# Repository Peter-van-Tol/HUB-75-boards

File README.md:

# HUB-75 boards

The HUB-75 boards is a collection of break-out boards (BOBs) for HUB-75 connnectors found on re-purposed FPGA cards such as the 5A-75B and 5A-75E. These cards can be picked up for 10\~20 dollars from China and form an ideal basis for tinkering with FPGAs. Based on these cheap FPGA's a project has been spraked, called Litex-CNC, which aims to repurpose these cards to a cheap CNC controller. CNC-machines normally have field power which is 12\~24V and thus the FPGA cannot direclty be connected to the components of the machine. Therefore a set of break-out boards have been developed for GPIO inputs/outputs, stepgen, encoders, etc.

## Design philosophy
> Why not a hat one might ask? This project offers more flexibility. By combining different break-out can be combined to suit the machine that is being built. A hat also comes with a larger risk in design errors; smaller boards are easier to design, produce and check.

All BOBs will have the same dimensions of 85 mm x 56 mm. This size is equal to that of the Raspberry Pi 4, however the mounting holes are placed on the four corners and thus different from the RPi. Getting the mounting holes at the same location as the RPi made the design much more difficult. Placement of the connectors also hampers stacking these boards on top of each other, so not being to able to stack them on top of a RPi seems permissible.

The outputs of the BOBs will be on the bottom edge (long side). Field power and logic power are provided from the left side of the board. The HUB-75 connectors will be placed on the top of the boards. This makes it easier to route the digital signals and high-power signals separately from each other in the cabinet.

The smalles trace and spacing is 0.2 mm. These boards are designed to be ordered from an online PCB manufacturer. Some desktop milling machines might have the accuracy to create these traces, so you might give it a try when you are feeling lucky. The smallest holes (vias) are 0.3 mm in size.

All components are selected to be hand-solderable. This means that the following minimum sizes SMD components will be used:
- resistors, LED's, capacitors: SMD-1206
- diodes: SOD-123
- FET, transistors: SOT-23

## HUB-75 pinout
Each connector has 6 individual pins (1, 2, 3, 5, 6, and 7) and 8 shared pins (8 through 15). The standard pin-out of a HUB-75 connector is shown below.

| HUB75 pin | Pin   | Pin   | HUB75 pin |
|-----------|-------|-------|-----------|
| R0        | 1     | 2     | G0        |
| B0        | 3     | 4     | *GND*     |
| R1        | 5     | 6     | G1        |
| B1        | 7     | 8     | E         |
| A         | 9     | 10    | B         |
| C         | 11    | 12    | D         |
| CLK       | 13    | 14    | STB       |
| OE        | 15    | 16    | *GND*     |

Each HUB-75 connector will use the individual pins and in special cases one of the shared pins. In the design it should be taken into account that boards which uses the same shared pins might be mutual exclusive when the functions are different (different types of stepgen BOBs can off course be combined.

## Available BOBs
The table below shows the BOBs which are currently available in this repository, along with their status.

| Category  | Name                                                     | Description                                                     | HUB-75    | Status            |
|-----------|----------------------------------------------------------|-----------------------------------------------------------------|-----------|---------------------|
| stepgen   | [HUB75-Differential_stepgen](HUB75-Differential_stepgen) | 3 differential stepgen channels, frequency up to 400 kHz        | 2 + 0.5   | Prototype-2 ordered | 
| GPIO-out  | [HUB75-Sourcing_output](HUB75-Sourcing_output)           | 12 channel sourcing output (<1 kHz, 4 A per channel, 4 A total) | 2         | Prototype-2 ordered | 
| GPIO-in   | [HUB75-Sinking_input](HUB75-Sinking_input)               | 12 channel sinking input (< 1 kHz)                              | 2         | Untested          |

## Connecting the BOBs to your FPGA
On both the 5A-75B and the 5A-75E the `74HC245T` buffers are hard-wired as outputs. To be able to use the HUB-75 boards which require an input (as seen from the FPGA) some modifications on the board are required. Of both boards different versiosn exist, so the components can be at a different location on your board. Below are the locations of the buffer on a 5A-75B V6.1 (front) and 5A-75E V6.0 (back).

Each buffer has 8 channels, while every HUB-75 connector has 6 individual pins. When you replace a buffer you will cahnge the behavior of one HUB-75 connector and partly that of its neighbor. All HUB-75 boards assume that a connector is either fully configured as input or as output. Therefore it is recommended to change the buffers direclty adjacent to each other, so the minimum amount of available connectors (partly input/ouput) are wasted.

The following changes have to be made to the buffers:
* De-solder the `74HC245T` buffer, this buffer cannot be re-used because its pins are not 5 Volt tolerant when `Vcc` is 3.3 Volt.
* Cut the trace to the pin `Vcc` (pin 20) and wire it to a 3.3V source (for example the JTAG-header). If you don't do this, a buffer configure as input will put 5 Volts on the pins of the FPGA, which will definately fry that pin or the whole board.
* Cut the trace to the pin `DIR` (pin 20) and wire it to a GND source to configure the buffer as input.
* Replace the buffer with a buffer with 5V tolerant inputs, such as the `74LVC245` ([datasheet](https://www.ti.com/lit/ds/symlink/sn74lvc245a.pdf)).

After these modifications the board might look a like this (on this particular board a single buffer has been replace, as it is a test-board for LitexCNC).

TODO: picture to be taken

## License 
The boards in this repository are licensed unde Creative Commons BY-NC-SA. This means you are allowed to:
* **Share** — copy and redistribute the material in any medium or format
* **Adapt** — remix, transform, and build upon the material

As long as:
* **Attribution** — You must give appropriate credit, provide a link to the license, and indicate if changes were made. You may do so in any reasonable manner, but not in any way that suggests the licensor endorses you or your use.
* **NonCommercial** — You may not use the material for  commercial purposes. Of course you can use the machine you created or modified using these boards for commercial purposes. 
* **ShareAlike** — If you remix, transform, or build upon the material, you must distribute your contributions under the  same license  as the original.

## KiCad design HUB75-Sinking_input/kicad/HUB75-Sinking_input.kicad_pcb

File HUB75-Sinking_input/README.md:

# HUB-75 Sinking input 
Break-out board with 12 channel sinking input. The FPGA is galvanically separated from field power using opto-couplers.

## Features

- 2 HUB-75 output connectors
- 12 channel sinking output using JST connectors
- 5\~24 V Field power with reverse polarity protection
- indicating LED for each output
- indicated switching frequency 1 kHz

## Applications

- PNP (souring) limit switches
- Momentary push-buttons
- Slow encoders, for example for user input

> **NOTE** <br> The `PC827` optocouplers have a maximum rated frequency of 80 kHz. It is recommended to start at a frequency of 1 kHz and work up from there.

## Example wiring

TODO: example

## Litex-CNC example configuration
Let's assume that the two HUB-745 connectors on this board are connected to J15 and J16 of the FPGA. To configure the pins for output, you can use the configuration-block below as a starting point. Optionaly the pin names can also be set in the configuration, making the HAL clearer.

``` json
{
    ...,
    "gpio_in": [
        {"pin": "j15:0"},
        {"pin": "j15:1"},
        {"pin": "j15:2"},
        {"pin": "j15:4"},
        {"pin": "j15:5"},
        {"pin": "j15:6"},
        {"pin": "j16:0"},
        {"pin": "j16:1"},
        {"pin": "j16:2"},
        {"pin": "j16:4"},
        {"pin": "j16:5"},
        {"pin": "j16:6"}
    ],
    ...
}
```

Alternatively, the BOB can also be used for PWM output. In that case the configuration may look something like below. In this example it is assumed that outputs on J16 are used for three encoders.

``` json
{
    ...,
    "encoders": [
        {  
            "pin_A":"j16:0",
            "pin_B":"j16:1"
        },
        {  
            "pin_A":"j16:2",
            "pin_B":"j16:4"
        },
        {  
            "pin_A":"j16:5",
            "pin_B":"j16:6"
        }
    ],
    ...
}
```

## Bill of materials

The table below gives the bill of materials used for this BOB and an indication of its price. The list is available as public list for the following companies:
* [Reichtelt](https://www.reichelt.de/my/1998173). This is non-affiliate link, I do not earn any money when you order this list from this specific vendor, nor the vendor endorses this project. Reichtelt is a supplyer for Western Europe.

When you order with Mouser or antohter supplier, please share a list here.

| Part. number | Package   | Description                        | Datasheet | Amount | Price*  |
|--------------|-----------|------------------------------------|-----------|--------|---------|
| LTV827       | DIP-8     | Dual-channel opto-coupler          |           | 6      | € 0.31  |
| AO3401A      | SOT-23    | P-Channel MOSFET, 30V              |           | 1      | € 0.25  |
| ZENER 12V    | SOT-23    | 12V Zener diode***                 |           | 1      | € 0.05  |
| 4.7K         | SMD 1206  | Resistor, 4.7 kOhm                 |           | 12     | € 0.03  |
| 10K          | SMD 1206  | Resistor, 10 kOhm                  |           | 1      | € 0.03  |
| LED          | SMD 1206  | LED, green, If > 20 mA             |           | 12     | € 0.08  |
| CAP 15N      | SMD 1206  | Capitor, 15 nF                     |           | 1      | € 0.02  |
| JST XH 3P    | -         | JST XH conn. 2.5 mm pitch          |           | 12     | € 0.15  |
| DG250 3,5-2  | -         | Screw/spring terminal 2.5 mm pitch |           | 2      | € 0.22  |
| BOX 2X8      | -         | Box header 2x8, 2.54 mm pitch      |           | 2      | € 0.16  |
| 2N7002**     | SOT-23    | N-Channel MOSFET (current mirror)  |           | 13     | € 0.04  |
| CL2N8-G**    | SOT-89    | LED-driver 20 mA (current mirror)  |           | 1      | € 0.39  |
| R**          | SMD 1206  | Resistor, TBD Ohm (alternative)    |           | 12     | € 0.03  |

**NOTES**: 
1. The price is based on availability in the Netherlands with a single shop for all parts. Parts might be sourced cheaper depending on your location, available sources and the time you want to wait before receiving the components.
2. The components `CL2N8-G` and `2N7002` form a current mirror for driving the status LEDs. This current mirror can be replaced with a fixed resistor `R`, which should be calculated based on the voltage used for Field power.
3. The zener diode is only required when Field Power is >12 Volt for protecting the MOSFETs.

## Known issues

This board does not have any known issues yet.

If you find any issue, please file a bug using GitHub.

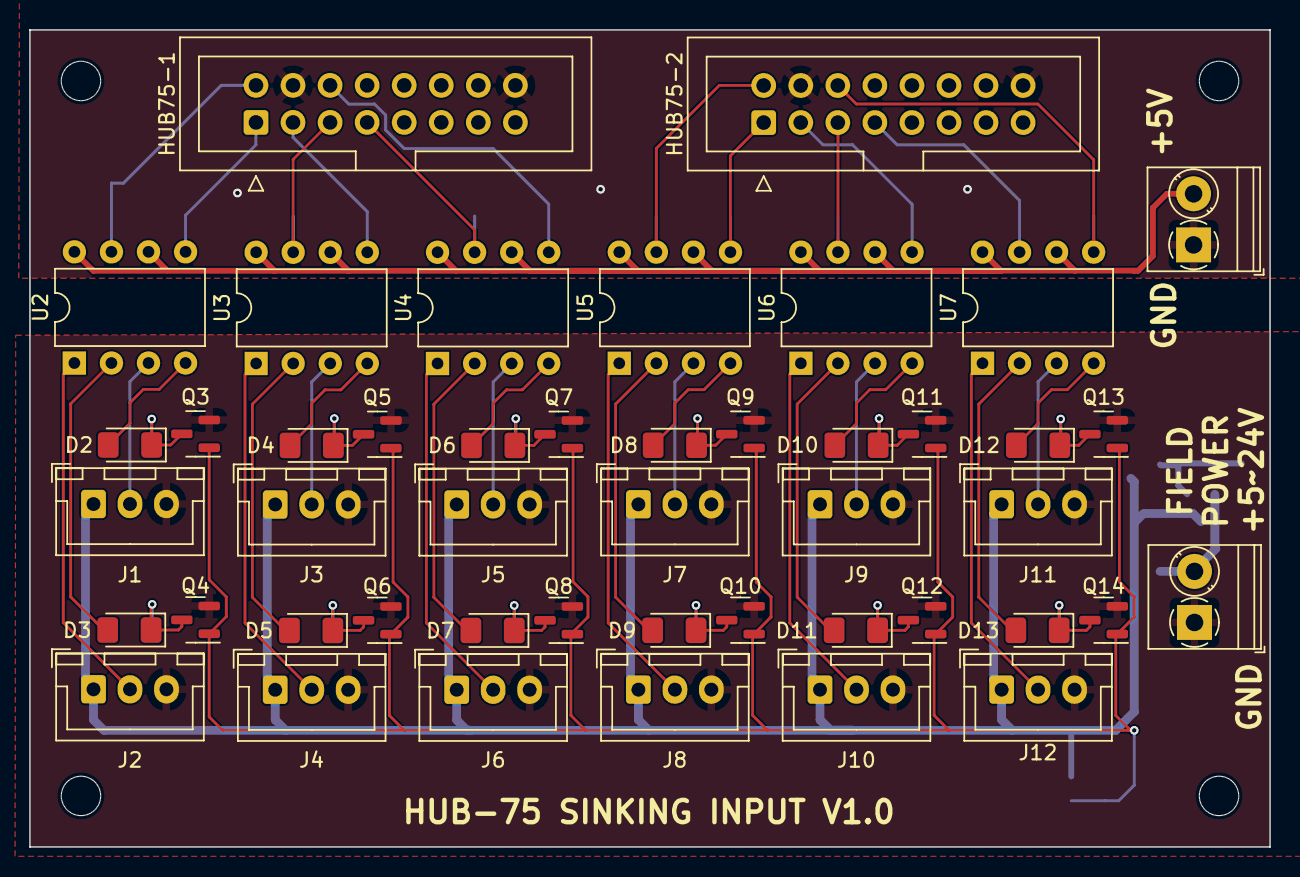
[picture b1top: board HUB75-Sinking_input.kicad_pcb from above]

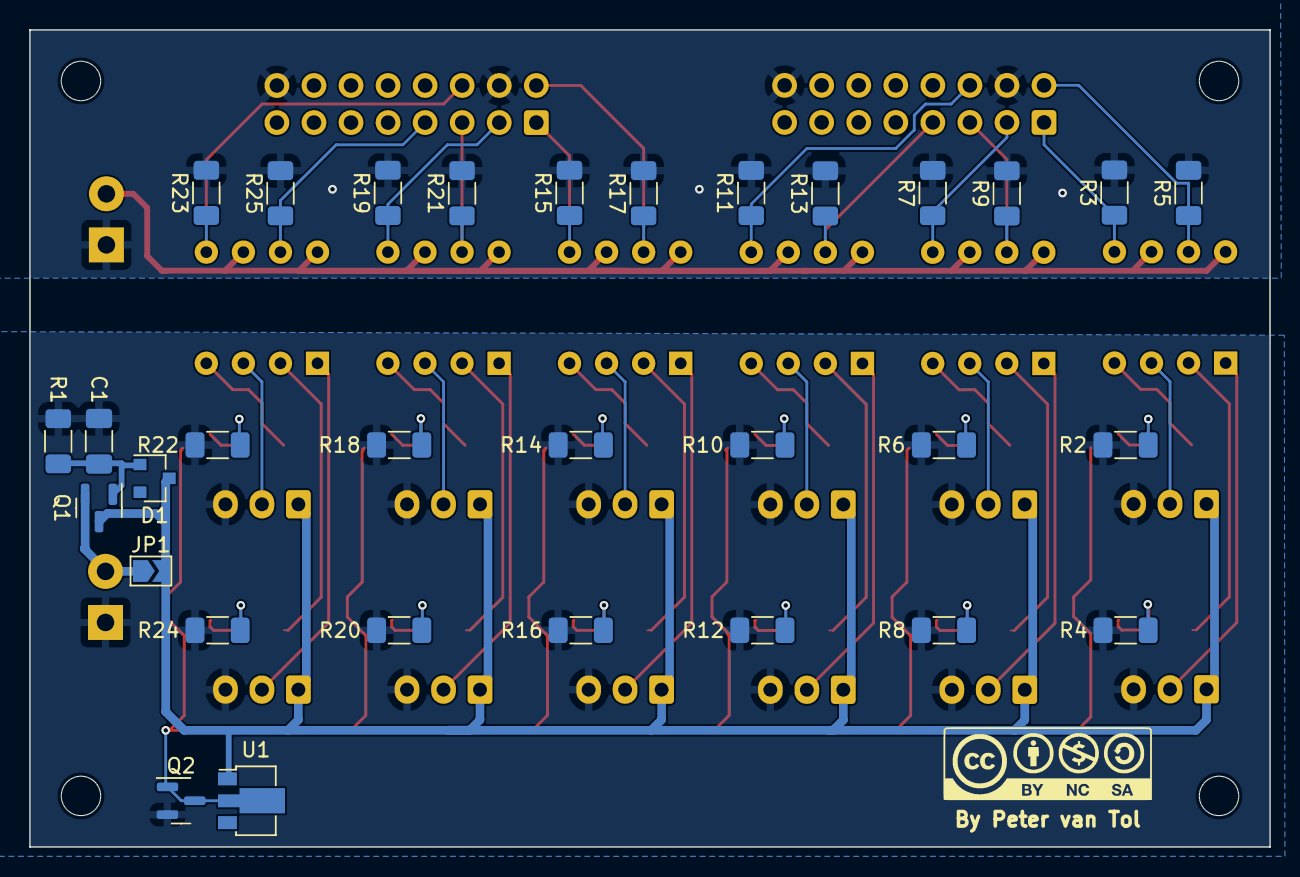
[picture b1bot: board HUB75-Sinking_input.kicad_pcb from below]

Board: 2 copper layers, 85.0 x 56.0 mm, 81 parts (31 on the bottom side), 55 nets.

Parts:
C1: 15nF; C_1206_3216Metric_Pad1.33x1.80mm_HandSolder
D1: D_Zener; D_SOT-23_ANK
D2, D3, D4, D5, D6, D7, D8, D9, D10, D11, D12, D13: LED_Small; LED_1206_3216Metric_Pad1.42x1.75mm_HandSolder
HOLE1, HOLE2, HOLE3, HOLE4: MountingHole_2.7mm_M2.5_DIN965
HUB75-1, HUB75-2: Conn_02x08_Odd_Even; IDC-Header_2x08_P2.54mm_Vertical
J1, J2, J3, J4, J5, J6, J7, J8, J9, J10, J11, J12: Conn_01x03_Male; JST_XH_B3B-XH-A_1x03_P2.50mm_Vertical
JP1: Jumper_2_Open; SolderJumper-2_P1.3mm_Open_TrianglePad1.0x1.5mm
PWR1, PWR2: Screw_Terminal_01x02; TerminalBlock_Phoenix_PT-1,5-2-3.5-H_1x02_P3.50mm_Horizontal
Q1: AO3401A; SOT-23
Q2, Q3, Q4, Q5, Q6, Q7, Q8, Q9, Q10, Q11, Q12, Q13, Q14: 2N7002; SOT-23
R1: 10K; R_1206_3216Metric_Pad1.30x1.75mm_HandSolder
R2, R4, R6, R8, R10, R12, R14, R16, R18, R20, R22, R24: R; R_1206_3216Metric_Pad1.30x1.75mm_HandSolder
R3, R5, R7, R9, R11, R13, R15, R17, R19, R21, R23, R25: 4.7K; R_1206_3216Metric_Pad1.30x1.75mm_HandSolder
U1: CL2N8-G; SOT-89-3
U2, U3, U4, U5, U6, U7: LTV-827; DIP-8_W7.62mm

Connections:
+5V: PWR2.2, U2.6, U2.8, U3.6, U3.8, U4.6, U4.8, U5.6, U5.8, U6.6, U6.8, U7.6, U7.8
CUR_MIRROR: Q2.1 (G), Q2.3 (D), Q3.1 (G), Q4.1 (G), Q5.1 (G), Q6.1 (G), Q7.1 (G), Q8.1 (G), Q9.1 (G), Q10.1 (G), Q11.1 (G), Q12.1 (G), Q13.1 (G), Q14.1 (G), U1.2 (GND)
GND: HUB75-1.4, HUB75-1.16, HUB75-2.4, HUB75-2.16, PWR2.1, R3.2, R5.2, R7.2, R9.2, R11.2, R13.2, R15.2, R17.2, R19.2, R21.2, R23.2, R25.2
GNDD: C1.2, J1.3, J2.3, J3.3, J4.3, J5.3, J6.3, J7.3, J8.3, J9.3, J10.3, J11.3, J12.3, PWR1.1, Q2.2 (S), Q3.2 (S), Q4.2 (S), Q5.2 (S), Q6.2 (S), Q7.2 (S), Q8.2 (S), Q9.2 (S), Q10.2 (S), Q11.2 (S), Q12.2 (S), Q13.2 (S), Q14.2 (S), R1.2, R2.1, R4.1, R6.1, R8.1, R10.1, R12.1, R14.1, R16.1, R18.1, R20.1, R22.1, R24.1
GPIO1-1: HUB75-1.1, R3.1, U2.5
GPIO1-2: HUB75-1.2, R5.1, U2.7
GPIO1-3: HUB75-1.3, R7.1, U3.5
GPIO1-4: HUB75-1.5, R9.1, U3.7
GPIO1-5: HUB75-1.6, R11.1, U4.5
GPIO1-6: HUB75-1.7, R13.1, U4.7
GPIO2-1: HUB75-2.1, R15.1, U5.5
GPIO2-2: HUB75-2.2, R17.1, U5.7
GPIO2-3: HUB75-2.3, R19.1, U6.5
GPIO2-4: HUB75-2.5, R21.1, U6.7
GPIO2-5: HUB75-2.6, R23.1, U7.5
GPIO2-6: HUB75-2.7, R25.1, U7.7
unnamed: C1.1, D1.2 (A), Q1.1 (G), R1.1
unnamed: D2.1 (K), Q3.3 (D), R2.2
unnamed: D2.2 (A), U2.4
unnamed: D3.1 (K), Q4.3 (D), R4.2
unnamed: D3.2 (A), U2.2
unnamed: D4.1 (K), Q5.3 (D), R6.2
unnamed: D4.2 (A), U3.4
unnamed: D5.1 (K), Q6.3 (D), R8.2
unnamed: D5.2 (A), U3.2
unnamed: D6.1 (K), Q7.3 (D), R10.2
unnamed: D6.2 (A), U4.4
unnamed: D7.1 (K), Q8.3 (D), R12.2
unnamed: D7.2 (A), U4.2
unnamed: D8.1 (K), Q9.3 (D), R14.2
unnamed: D8.2 (A), U5.4
unnamed: D9.1 (K), Q10.3 (D), R16.2
unnamed: D9.2 (A), U5.2
unnamed: D10.1 (K), Q11.3 (D), R18.2
unnamed: D10.2 (A), U6.4
unnamed: D11.1 (K), Q12.3 (D), R20.2
unnamed: D11.2 (A), U6.2
unnamed: D12.1 (K), Q13.3 (D), R22.2
unnamed: D12.2 (A), U7.4
unnamed: D13.1 (K), Q14.3 (D), R24.2
unnamed: D13.2 (A), U7.2
unnamed: J1.2, U2.3
unnamed: J2.2, U2.1
unnamed: J3.2, U3.3
unnamed: J4.2, U3.1
unnamed: J5.2, U4.3
unnamed: J6.2, U4.1
unnamed: J7.2, U5.3
unnamed: J8.2, U5.1
unnamed: J9.2, U6.3
unnamed: J10.2, U6.1
unnamed: J11.2, U7.3
unnamed: J12.2, U7.1
unnamed: JP1.1 (A), PWR1.2, Q1.2 (S)
VDD: D1.1 (K), J1.1, J2.1, J3.1, J4.1, J5.1, J6.1, J7.1, J8.1, J9.1, J10.1, J11.1, J12.1, JP1.2 (B), Q1.3 (D), U1.1 (VDD)

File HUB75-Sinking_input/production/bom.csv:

Designator,Footprint,Quantity,Value,LCSC Part #
C1,C_1206_3216Metric_Pad1.33x1.80mm_HandSolder,1,15nF,
D1,D_SOD-123,1,D_Zener,
"D10, D11, D12, D13, D2, D3, D4, D5, D6, D7, D8, D9",LED_1206_3216Metric_Pad1.42x1.75mm_HandSolder,12,LED_Small,
"HUB75-1, HUB75-2",PinHeader_2x08_P2.54mm_Vertical,2,Conn_02x08_Odd_Even,
"J1, J10, J11, J12, J2, J3, J4, J5, J6, J7, J8, J9",JST_XH_B3B-XH-A_1x03_P2.50mm_Vertical,12,Conn_01x03_Male,
"PWR1, PWR2","TerminalBlock_Phoenix_PT-1,5-2-3.5-H_1x02_P3.50mm_Horizontal",2,Screw_Terminal_01x02,
Q1,SOT-23,1,AO3401A,
"Q10, Q11, Q12, Q13, Q14, Q2, Q3, Q4, Q5, Q6, Q7, Q8, Q9",SOT-23,13,2N7002,
R1,R_1206_3216Metric_Pad1.30x1.75mm_HandSolder,1,10K,
"R10, R12, R14, R16, R18, R2, R20, R22, R24, R4, R6, R8",R_1206_3216Metric_Pad1.30x1.75mm_HandSolder,12,R,
"R11, R13, R15, R17, R19, R21, R23, R25, R3, R5, R7, R9",R_1206_3216Metric_Pad1.30x1.75mm_HandSolder,12,4.7K,
U1,SOT-89-3,1,CL2N8-G,
"U2, U3, U4, U5, U6, U7",DIP-8_W7.62mm,6,LTV-827,

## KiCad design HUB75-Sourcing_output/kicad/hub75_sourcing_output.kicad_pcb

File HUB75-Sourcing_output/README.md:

# HUB-75 Sourcing output 
Break-out board with 12 channel sourcing output. The FPGA is galvanically separated from field power using opto-couplers. To enhance the power each channel can deliver, the loads are being switched with a MOSfet (`AO3401A`). 

## Features

- 2 HUB-75 input connectors
- 12 channel sourcing output using JST connectors
- 5\~24 V Field power with reverse polarity protection
- rated 300 mA power per channel
- indicating LED for each output
- indicated switching frequency 1 kHz

## Applications

- Driving LEDs (optional dimmable by using PWM)
- Driving solenoids with current lower then rated current
- Driving relays for larger loads 

> **NOTE** <br> The `PC827` optocouplers have a maximum rated frequency of 80 kHz. When using this board in combination with PWM, the chosen frequency should be well below this limit. It is recommended to start at a frequency of 1 kHz and work up from there. PDM with LitexCNC will not work with this board, because the frequency cannot be set and will be too high. 

## Example wiring

TODO: example

> **NOTE** <br> When connecting any inductive loads, please connect a fly-back diode!

## Litex-CNC example configuration
Let's assume that the two HUB-745 connectors on this board are connected to J1 and J2 of the FPGA. To configure the pins for output, you can use the configuration-block below as a starting point. Optionaly the pin names can also be set in the configuration, making the HAL clearer.

``` json
{
    ...,
    "gpio_out": [
        {"pin": "j1:0"},
        {"pin": "j1:1"},
        {"pin": "j1:2"},
        {"pin": "j1:4"},
        {"pin": "j1:5"},
        {"pin": "j1:6"},
        {"pin": "j2:0"},
        {"pin": "j2:1"},
        {"pin": "j2:2"},
        {"pin": "j2:4"},
        {"pin": "j2:5"},
        {"pin": "j2:6"}
    ],
    ...
}
```

Alternatively, the BOB can also be used for PWM output. In that case the configuration may look something like below. In this example it is assumed that outputs J10 through J12 on the BOB are used for PWM.

``` json
{
    ...,
    "gpio_out": [
        {"pin": "j1:0"},
        {"pin": "j1:1"},
        {"pin": "j1:2"},
        {"pin": "j1:4"},
        {"pin": "j1:5"},
        {"pin": "j1:6"},
        {"pin": "j2:0"},
        {"pin": "j2:1"},
        {"pin": "j2:2"}
    ],
    "pwm": [
        {"pin": "j2:4"},
        {"pin": "j2:5"},
        {"pin": "j2:6"}
    ]
    ...
}
```

When using PWM, the HAL pin `pwm.###.pwm_freq` should be set to a value smaller then 1000 (1 kHz). Higher frequencies can be tested using the board, by increasing this value. The uppper limit is 80 kHz, which is the maximum frequency of the `PC817` opto-coupler. 

## Bill of materials

The table below gives the bill of materials used for this BOB and an indication of its price. The list is available as public list for the following companies:
* [Reichtelt](https://www.reichelt.de/my/1997628). This is non-affiliate link, I do not earn any money when you order this list from this specific vendor, nor the vendor endorses this project. Reichtelt is a supplyer for Western Europe.

When you order with Mouser or antohter supplier, please share a list here.

| Part. number | Package   | Description                        | Datasheet | Amount | Price*  |
|--------------|-----------|------------------------------------|-----------|--------|---------|
| LTV827       | DIP-8     | Dual-channel opto-coupler          |           | 6      | € 0.31  |
| AO3401A      | SOT-23    | P-Channel MOSFET, 30V              |           | 13     | € 0.25  |
| ZENER 12V    | SOT-23    | 12V Zener diode***                 |           | 13     | € 0.05  |
| 200R         | SMD 1206  | Resistor, 200 Ohm                  |           | 12     | € 0.03  |
| 240          | SMD 1206  | Resistor, 240 Ohm                  |           | 12     | € 0.03  |
| 10K          | SMD 1206  | Resistor, 10 kOhm                  |           | 13     | € 0.03  |
| LED          | SMD 1206  | LED, green, If > 20 mA             |           | 12     | € 0.08  |
| CAP 15N      | SMD 1206  | Capitor, 15 nF                     |           | 1      | € 0.02  |
| JST XH 2P    | -         | JST XH conn. 2.5 mm pitch          |           | 12     | € 0.15  |
| DG250 3,5-2  | -         | Screw/spring terminal 2.5 mm pitch |           | 1      | € 0.22  |
| BOX 2X8      | -         | Box header 2x8, 2.54 mm pitch      |           | 2      | € 0.16  |
| 2N7002**     | SOT-23    | N-Channel MOSFET (current mirror)  |           | 13     | € 0.04  |
| CL2N8-G**    | SOT-89    | LED-driver 20 mA (current mirror)  |           | 1      | € 0.39  |
| R**          | SMD 1206  | Resistor, TBD Ohm (alternative)    |           | 12     | € 0.03  |

**NOTES**: 
1. The price is based on availability in the Netherlands with a single shop for all parts. Parts might be sourced cheaper depending on your location, available sources and the time you want to wait before receiving the components.
2. The components `CL2N8-G` and `2N7002` form a current mirror for driving the status LEDs. This current mirror can be replaced with a fixed resistor `R`, which should be calculated based on the voltage used for Field power.
3. The zener diode is only required when Field Power is >12 Volt for protecting the MOSFETs.

## Known issues

- The reverse voltage protection uses a footprint for the resistor which is too large in the prototype (component not available). In the next version this footprint is modified to the default SMD 1206. Also the cpacitor is a through-hole component, as the value was wrong. The value is corrected in the BOM. In the next version this component is also replaced to SMD 1206.
- Current mirror is to be tested whether it works reliable.

If you find more issues, please file a bug using GitHub.

# Version history

**1.1**
* Corrected P-channel MOSFET's, the source and drain where switched, which prevented the V1.0 board from working. 
* Changed pin-headers to IDC-headers. Rerouted because of more space required by the IDC-header
* Corrected footprint of reverse current protection. Added jumper to be able to by-pass this circuit. 

**1.0**
* Initial version for proto-type.

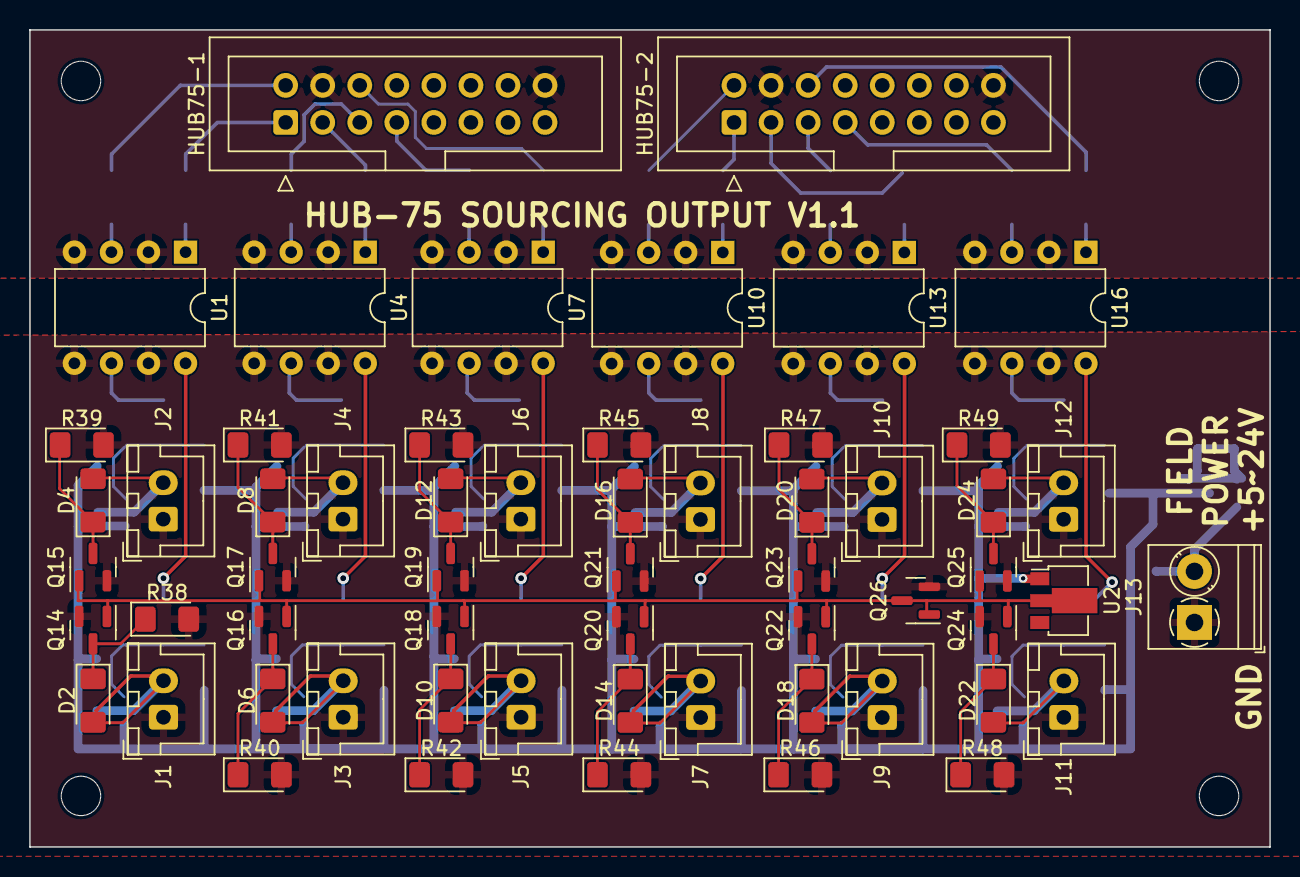
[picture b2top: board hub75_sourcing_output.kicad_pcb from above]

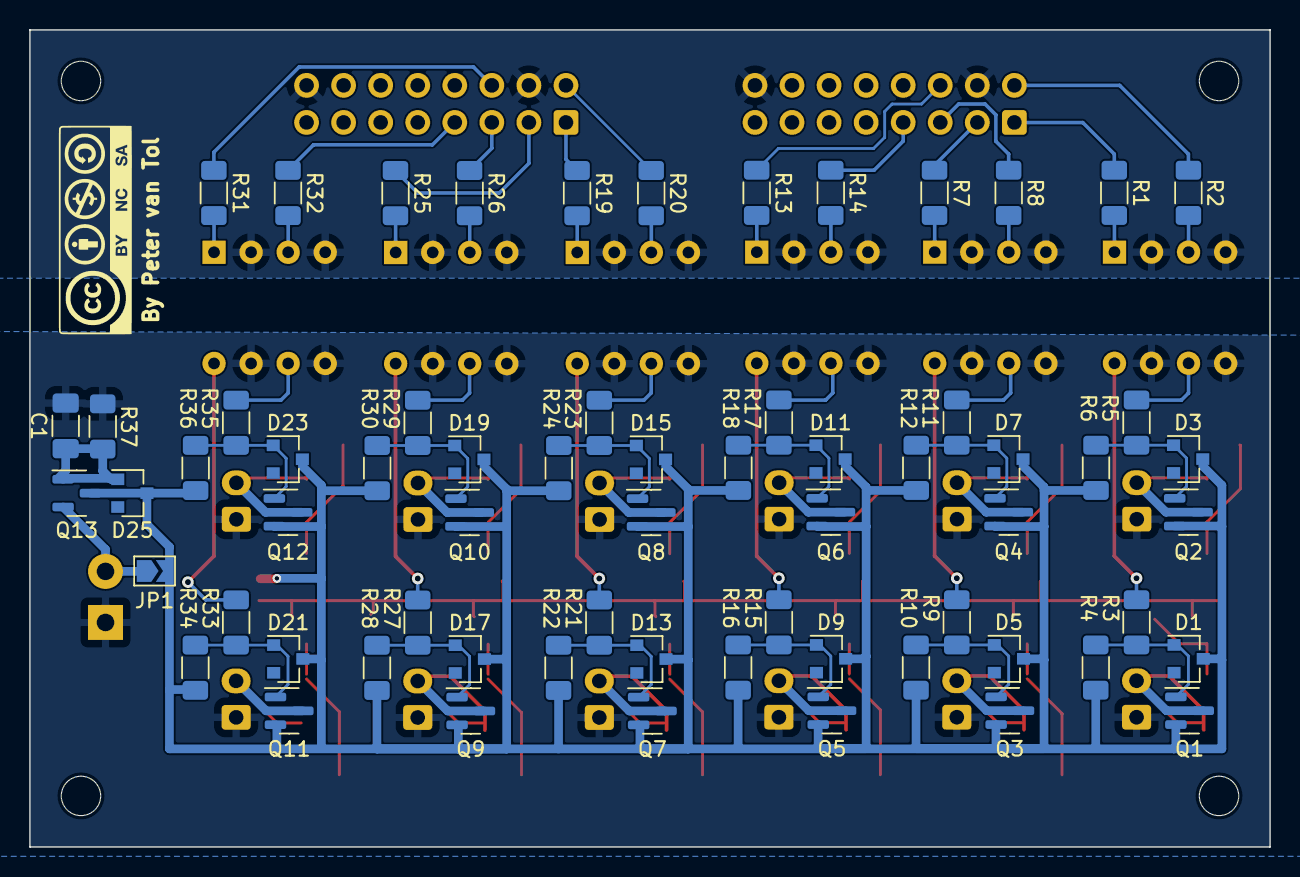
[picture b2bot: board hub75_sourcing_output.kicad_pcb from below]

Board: 2 copper layers, 85.0 x 56.0 mm, 128 parts (65 on the bottom side), 78 nets.

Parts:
C1: 15uF; C_1206_3216Metric_Pad1.33x1.80mm_HandSolder
D1, D3, D5, D7, D9, D11, D13, D15, D17, D19, D21, D23, D25: D_Zener; D_SOT-23_ANK
D2, D4, D6, D8, D10, D12, D14, D16, D18, D20, D22, D24: LED_Small; LED_1206_3216Metric_Pad1.42x1.75mm_HandSolder
HOLE1, HOLE2, HOLE3, HOLE4: MountingHole_2.7mm_M2.5_DIN965
HUB75-1, HUB75-2: Conn_02x08_Odd_Even; IDC-Header_2x08_P2.54mm_Vertical
J1, J2, J3, J4, J5, J6, J7, J8, J9, J10, J11, J12: Conn_01x02_Male; JST_XH_B2B-XH-A_1x02_P2.50mm_Vertical
J13: Screw_Terminal_01x02; TerminalBlock_Phoenix_PT-1,5-2-3.5-H_1x02_P3.50mm_Horizontal
JP1: Jumper_2_Open; SolderJumper-2_P1.3mm_Open_TrianglePad1.0x1.5mm
Q1, Q2, Q3, Q4, Q5, Q6, Q7, Q8, Q9, Q10, Q11, Q12: BSS84; SOT-23
Q13: AO3401A; SOT-23
Q14, Q15, Q16, Q17, Q18, Q19, Q20, Q21, Q22, Q23, Q24, Q25, Q26: 2N7002; SOT-23
R1, R2, R7, R8, R13, R14, R19, R20, R25, R26, R31, R32: 240R; R_1206_3216Metric_Pad1.30x1.75mm_HandSolder
R3, R5, R9, R11, R15, R17, R21, R23, R27, R29, R33, R35: 200R; R_1206_3216Metric_Pad1.30x1.75mm_HandSolder
R4, R6, R10, R12, R16, R18, R22, R24, R28, R30, R34, R36, R37: 10K; R_1206_3216Metric_Pad1.30x1.75mm_HandSolder
R38, R39, R40, R41, R42, R43, R44, R45, R46, R47, R48, R49: R; LED_1206_3216Metric_Pad1.42x1.75mm_HandSolder
U1, U4, U7, U10, U13, U16: LTV-827; DIP-8_W7.62mm
U2: CL2N8-G; SOT-89-3

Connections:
/opto_coupler_channel1/FET-driver1/SIGNAL_IN: R9.2, U4.8
/opto_coupler_channel1/FET-driver2/SIGNAL_IN: R11.2, U4.6
/opto_coupler_channel2/FET-driver1/SIGNAL_IN: R15.2, U7.8
/opto_coupler_channel2/FET-driver2/SIGNAL_IN: R17.2, U7.6
/opto_coupler_channel3/FET-driver1/SIGNAL_IN: R21.2, U10.8
/opto_coupler_channel3/FET-driver2/SIGNAL_IN: R23.2, U10.6
/opto_coupler_channel4/FET-driver1/SIGNAL_IN: R27.2, U13.8
/opto_coupler_channel4/FET-driver2/SIGNAL_IN: R29.2, U13.6
/opto_coupler_channel5/FET-driver1/SIGNAL_IN: R33.2, U16.8
/opto_coupler_channel5/FET-driver2/SIGNAL_IN: R35.2, U16.6
/opto_coupler_channel/FET-driver1/SIGNAL_IN: R3.2, U1.8
/opto_coupler_channel/FET-driver2/SIGNAL_IN: R5.2, U1.6
CUR_MIRROR: Q14.1 (G), Q15.1 (G), Q16.1 (G), Q17.1 (G), Q18.1 (G), Q19.1 (G), Q20.1 (G), Q21.1 (G), Q22.1 (G), Q23.1 (G), Q24.1 (G), Q25.1 (G), Q26.1 (G), Q26.3 (D), U2.2 (GND)
GND: HUB75-1.4, HUB75-1.16, HUB75-2.4, HUB75-2.16, U1.2, U1.4, U4.2, U4.4, U7.2, U7.4, U10.2, U10.4, U13.2, U13.4, U16.2, U16.4
GNDD: C1.2, J1.1, J2.1, J3.1, J4.1, J5.1, J6.1, J7.1, J8.1, J9.1, J10.1, J11.1, J12.1, J13.1, Q14.2 (S), Q15.2 (S), Q16.2 (S), Q17.2 (S), Q18.2 (S), Q19.2 (S), Q20.2 (S), Q21.2 (S), Q22.2 (S), Q23.2 (S), Q24.2 (S), Q25.2 (S), Q26.2 (S), R37.2, R38.2, R39.2, R40.2, R41.2, R42.2, R43.2, R44.2, R45.2, R46.2, R47.2, R48.2, R49.2, U1.5, U1.7, U4.5, U4.7, U7.5, U7.7, U10.5, U10.7, U13.5, U13.7, U16.5, U16.7
GPIO1-1: HUB75-1.1, R1.1
GPIO1-2: HUB75-1.2, R2.1
GPIO1-3: HUB75-1.3, R7.1
GPIO1-4: HUB75-1.5, R8.1
GPIO1-5: HUB75-1.6, R13.1
GPIO1-6: HUB75-1.7, R14.1
GPIO2-1: HUB75-2.1, R19.1
GPIO2-2: HUB75-2.2, R20.1
GPIO2-3: HUB75-2.3, R25.1
GPIO2-4: HUB75-2.5, R26.1
GPIO2-5: HUB75-2.6, R31.1
GPIO2-6: HUB75-2.7, R32.1
unnamed: C1.1, D25.2 (A), Q13.1 (G), R37.1
unnamed: D1.2 (A), Q1.1 (G), R3.1, R4.2
unnamed: D2.1 (K), Q14.3 (D), R38.1
unnamed: D2.2 (A), J1.2, Q1.3 (D)
unnamed: D3.2 (A), Q2.1 (G), R5.1, R6.2
unnamed: D4.1 (K), Q15.3 (D), R39.1
unnamed: D4.2 (A), J2.2, Q2.3 (D)
unnamed: D5.2 (A), Q3.1 (G), R9.1, R10.2
unnamed: D6.1 (K), Q16.3 (D), R40.1
unnamed: D6.2 (A), J3.2, Q3.3 (D)
unnamed: D7.2 (A), Q4.1 (G), R11.1, R12.2
unnamed: D8.1 (K), Q17.3 (D), R41.1
unnamed: D8.2 (A), J4.2, Q4.3 (D)
unnamed: D9.2 (A), Q5.1 (G), R15.1, R16.2
unnamed: D10.1 (K), Q18.3 (D), R42.1
unnamed: D10.2 (A), J5.2, Q5.3 (D)
unnamed: D11.2 (A), Q6.1 (G), R17.1, R18.2
unnamed: D12.1 (K), Q19.3 (D), R43.1
unnamed: D12.2 (A), J6.2, Q6.3 (D)
unnamed: D13.2 (A), Q7.1 (G), R21.1, R22.2
unnamed: D14.1 (K), Q20.3 (D), R44.1
unnamed: D14.2 (A), J7.2, Q7.3 (D)
unnamed: D15.2 (A), Q8.1 (G), R23.1, R24.2
unnamed: D16.1 (K), Q21.3 (D), R45.1
unnamed: D16.2 (A), J8.2, Q8.3 (D)
unnamed: D17.2 (A), Q9.1 (G), R27.1, R28.2
unnamed: D18.1 (K), Q22.3 (D), R46.1
unnamed: D18.2 (A), J9.2, Q9.3 (D)
unnamed: D19.2 (A), Q10.1 (G), R29.1, R30.2
unnamed: D20.1 (K), Q23.3 (D), R47.1
unnamed: D20.2 (A), J10.2, Q10.3 (D)
unnamed: D21.2 (A), Q11.1 (G), R33.1, R34.2
unnamed: D22.1 (K), Q24.3 (D), R48.1
unnamed: D22.2 (A), J11.2, Q11.3 (D)
unnamed: D23.2 (A), Q12.1 (G), R35.1, R36.2
unnamed: D24.1 (K), Q25.3 (D), R49.1
unnamed: D24.2 (A), J12.2, Q12.3 (D)
unnamed: J13.2, JP1.1 (A), Q13.2 (S)
unnamed: R1.2, U1.1
unnamed: R2.2, U1.3
unnamed: R7.2, U4.1
unnamed: R8.2, U4.3
unnamed: R13.2, U7.1
unnamed: R14.2, U7.3
unnamed: R19.2, U10.1
unnamed: R20.2, U10.3
unnamed: R25.2, U13.1
unnamed: R26.2, U13.3
unnamed: R31.2, U16.1
unnamed: R32.2, U16.3
VDD: D1.1 (K), D3.1 (K), D5.1 (K), D7.1 (K), D9.1 (K), D11.1 (K), D13.1 (K), D15.1 (K), D17.1 (K), D19.1 (K), D21.1 (K), D23.1 (K), D25.1 (K), JP1.2 (B), Q1.2 (S), Q2.2 (S), Q3.2 (S), Q4.2 (S), Q5.2 (S), Q6.2 (S), Q7.2 (S), Q8.2 (S), Q9.2 (S), Q10.2 (S), Q11.2 (S), Q12.2 (S), Q13.3 (D), R4.1, R6.1, R10.1, R12.1, R16.1, R18.1, R22.1, R24.1, R28.1, R30.1, R34.1, R36.1, U2.1 (VDD)

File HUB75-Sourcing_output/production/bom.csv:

Designator,Footprint,Quantity,Value,LCSC Part #
C1,C_1206_3216Metric_Pad1.33x1.80mm_HandSolder,1,15uF,
"D1, D11, D13, D15, D17, D19, D21, D23, D25, D3, D5, D7, D9",D_SOT-23_ANK,13,D_Zener,
"D10, D12, D14, D16, D18, D2, D20, D22, D24, D4, D6, D8",LED_1206_3216Metric_Pad1.42x1.75mm_HandSolder,12,LED_Small,
"HUB75-1, HUB75-2",IDC-Header_2x08_P2.54mm_Vertical,2,Conn_02x08_Odd_Even,
"J1, J10, J11, J12, J2, J3, J4, J5, J6, J7, J8, J9",JST_XH_B2B-XH-A_1x02_P2.50mm_Vertical,12,Conn_01x02_Male,
J13,"TerminalBlock_Phoenix_PT-1,5-2-3.5-H_1x02_P3.50mm_Horizontal",1,Screw_Terminal_01x02,
JP1,SolderJumper-2_P1.3mm_Open_TrianglePad1.0x1.5mm,1,Jumper_2_Open,
"Q1, Q10, Q11, Q12, Q2, Q3, Q4, Q5, Q6, Q7, Q8, Q9",SOT-23,12,BSS84,
Q13,SOT-23,1,AO3401A,
"Q14, Q15, Q16, Q17, Q18, Q19, Q20, Q21, Q22, Q23, Q24, Q25, Q26",SOT-23,13,2N7002,
"R1, R13, R14, R19, R2, R20, R25, R26, R31, R32, R7, R8",R_1206_3216Metric_Pad1.30x1.75mm_HandSolder,12,240R,
"R10, R12, R16, R18, R22, R24, R28, R30, R34, R36, R37, R4, R6",R_1206_3216Metric_Pad1.30x1.75mm_HandSolder,13,10K,
"R11, R15, R17, R21, R23, R27, R29, R3, R33, R35, R5, R9",R_1206_3216Metric_Pad1.30x1.75mm_HandSolder,12,200R,
"U1, U10, U13, U16, U4, U7",DIP-8_W7.62mm,6,LTV-827,
U2,SOT-89-3,1,CL2N8-G,

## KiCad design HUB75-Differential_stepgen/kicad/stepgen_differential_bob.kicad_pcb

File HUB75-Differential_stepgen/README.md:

# HUB-75 Differential stepgen
Break-out board with 3 stepgen channels. As most stepper motor drivers are opto-isolated, the board does not provide any extra isolation.

> **NOTE** <br> On the images the RJ45-connectors and the SO-16 packages are not displayed as their models are not available in KiCAD.

## Features

- 2 HUB-75 input connectors
- 1 HUB-75 output connector for alarm
- 3 channel differential stepgen drivers using RJ-45 plugs with frequency up to 400 kHz
- status LEDs on RJ-45 plugs for Enable and Alarm
- selectable active HIGH or active LOW for Enable using dip-switches
- selectable active HIGH or active LOW for Alarm using dip-switches

Two differential stepgen BOBs can share HUB-75 output connector by setting the solder jumpers on the board for either stepgen 1-3 or stepgen 4-6.

## Applications

- Driving stepper motor drivers with internal opto-couplers.

> **NOTE** <br> To save on the number of outputs used, one can opt for a single ended version of the BOB.

## Example wiring

Any standard UTP-cable can be used for as a 'donor' for connecting the BOB to the driver. One can either:
- cut the cable and use the wires in the screw-terminals of the driver.
- create a small break-out board with RJ45 connector which fits your driver. The pitch *and* the order of the pins makes this a custom solution for almost any driver. These break-out boards, when developed, will be shared here as well, listed by type of the driver. These will be designed to be DIY, as small PCB's tend to be expensive.

The pin-out of the cable is as folllows

| RJ-45 pin | Color        | Function | 
|-----------|--------------|----------|
| 1         | green/white  | STEP-    |
| 2         | green        | STEP+    |
| 3         | orange/white | GND      |
| 4         | blue         | ENA      |
| 5         | blue/white   | GND      |
| 6         | orange       | ALARM    |
| 7         | brown/white  | DIR-     |
| 8         | brown        | DIR+     |

## Litex-CNC example configuration
Let's assume that the two output HUB-745 connectors on this board are connected to J1 and J2 of the FPGA and the input connector is J16. To configure the pins for output, you can use the configuration-block below as a starting point. Optionaly the pin names can also be set in the configuration, making the HAL clearer.

``` json
{
    ...,
    "stepgen": [
        {
            "step_pin": "j1:0",
            "dir_pin": "j1:1",
            "soft_stop": true
        },
        {
            "step_pin": "j1:2",
            "dir_pin": "j1:4",
            "soft_stop": true
        }
        {
            "step_pin": "j1:5",
            "dir_pin": "j1:6",
            "soft_stop": true
        },
        {
            "step_pin": "j2:0",
            "dir_pin": "j2:1",
            "soft_stop": true
        },
        {
            "step_pin": "j2:2",
            "dir_pin": "j2:4",
            "soft_stop": true
        }
        {
            "step_pin": "j2:5",
            "dir_pin": "j2:6",
            "soft_stop": true
        }
    ],
    "gpio_in": [
        {"pin": "j16:0", "name": "stepgen.0.alarm"},
        {"pin": "j16:1", "name": "stepgen.1.alarm"},
        {"pin": "j16:2", "name": "stepgen.2.alarm"},
        {"pin": "j16:4", "name": "stepgen.3.alarm"},
        {"pin": "j16:5", "name": "stepgen.4.alarm"},
        {"pin": "j16:6", "name": "stepgen.5.alarm"},
    ],
    "gpio_in": [
        {"pin": "j1:14", "name": "stepgen.enable"},
    ],
    ...
}
```

> **NOTE** <br> The BOB uses pin 14 (`OE`) of the HUB-75 connector, which is a shared pin. This board therefore cannot be used in combination with other BOB's using the same pin when it's function is incompatible.

## Bill of materials
The table below gives the bill of materials used for this BOB and an indication of its price. The list is available as public list for the following companies:
* [Reichtelt](https://www.reichelt.de/my/1997667). This is non-affiliate link, I do not earn any money when you order this list from this specific vendor, nor the vendor endorses this project. Reichtelt is a supplyer for Western Europe.

When you order with Mouser or antohter supplier, please share a list here.

| Part. number   | Package   | Description                        | Datasheet | Amount | Price*  |
|----------------|-----------|------------------------------------|-----------|--------|---------|
| 74HC86         | SO-16     | Quad XOR-gates                     |           | 2      | € 0.16  |
| SMD 1/4W270    | SMD 1206  | Resistor, 270 Ohm                  |           | 6      | € 0.03  |
| SMD 1/4W 10K   | SMD 1206  | Resistor, 10 kOhm                  |           | 12     | € 0.03  |
| X7R-G1206 100N | SMD 1206  | Capacittor 100 nF                  |           | 12     | € 0.22  |   
| DIP 3P         | DIP-6     | DIP-switch, 3P                     |           | 2      | € 0.33  |
| DG250 3,5-2    | -         | Screw/spring terminal 2.5 mm pitch |           | 1      | € 0.22  |
| BOX 2X8        | -         | Box header 2x8, 2.54 mm pitch      |           | 3      | € 0.16  |
| CAT5           | -         | RJ-45 Bus with LED**               |           | 3      | € 1.07  |

**NOTES**: 
1. The price is based on availability in the Netherlands with a single shop for all parts. Parts might be sourced cheaper depending on your location, available sources and the time you want to wait before receiving the components.
2. When using a different source for the connector, please verify the footprint, as there are many variants.

## Known issues

This board does not have any known issues yet.

If you find any issue, please file a bug using GitHub.

# Version history

**1.1**
* Changed HUB75 connectors from pin headers to IDC connectors (shrouded). Moved several components to make space for the larger footprint
* Wired alarm 1-3 to pin 1-3 of J3 (was pin 3-5-7, which was not logical for config). Wired alarm 4-6 to pin 5-7 of J3 (NOTE: pin 4 is GND). Version 1.0 boards cannot be connected to version 1.1 boards due to this change.
* Added labels to clarify the function of the DIP-switches and solder jumpers. 

**1.0**
* Initial version for proto-type.

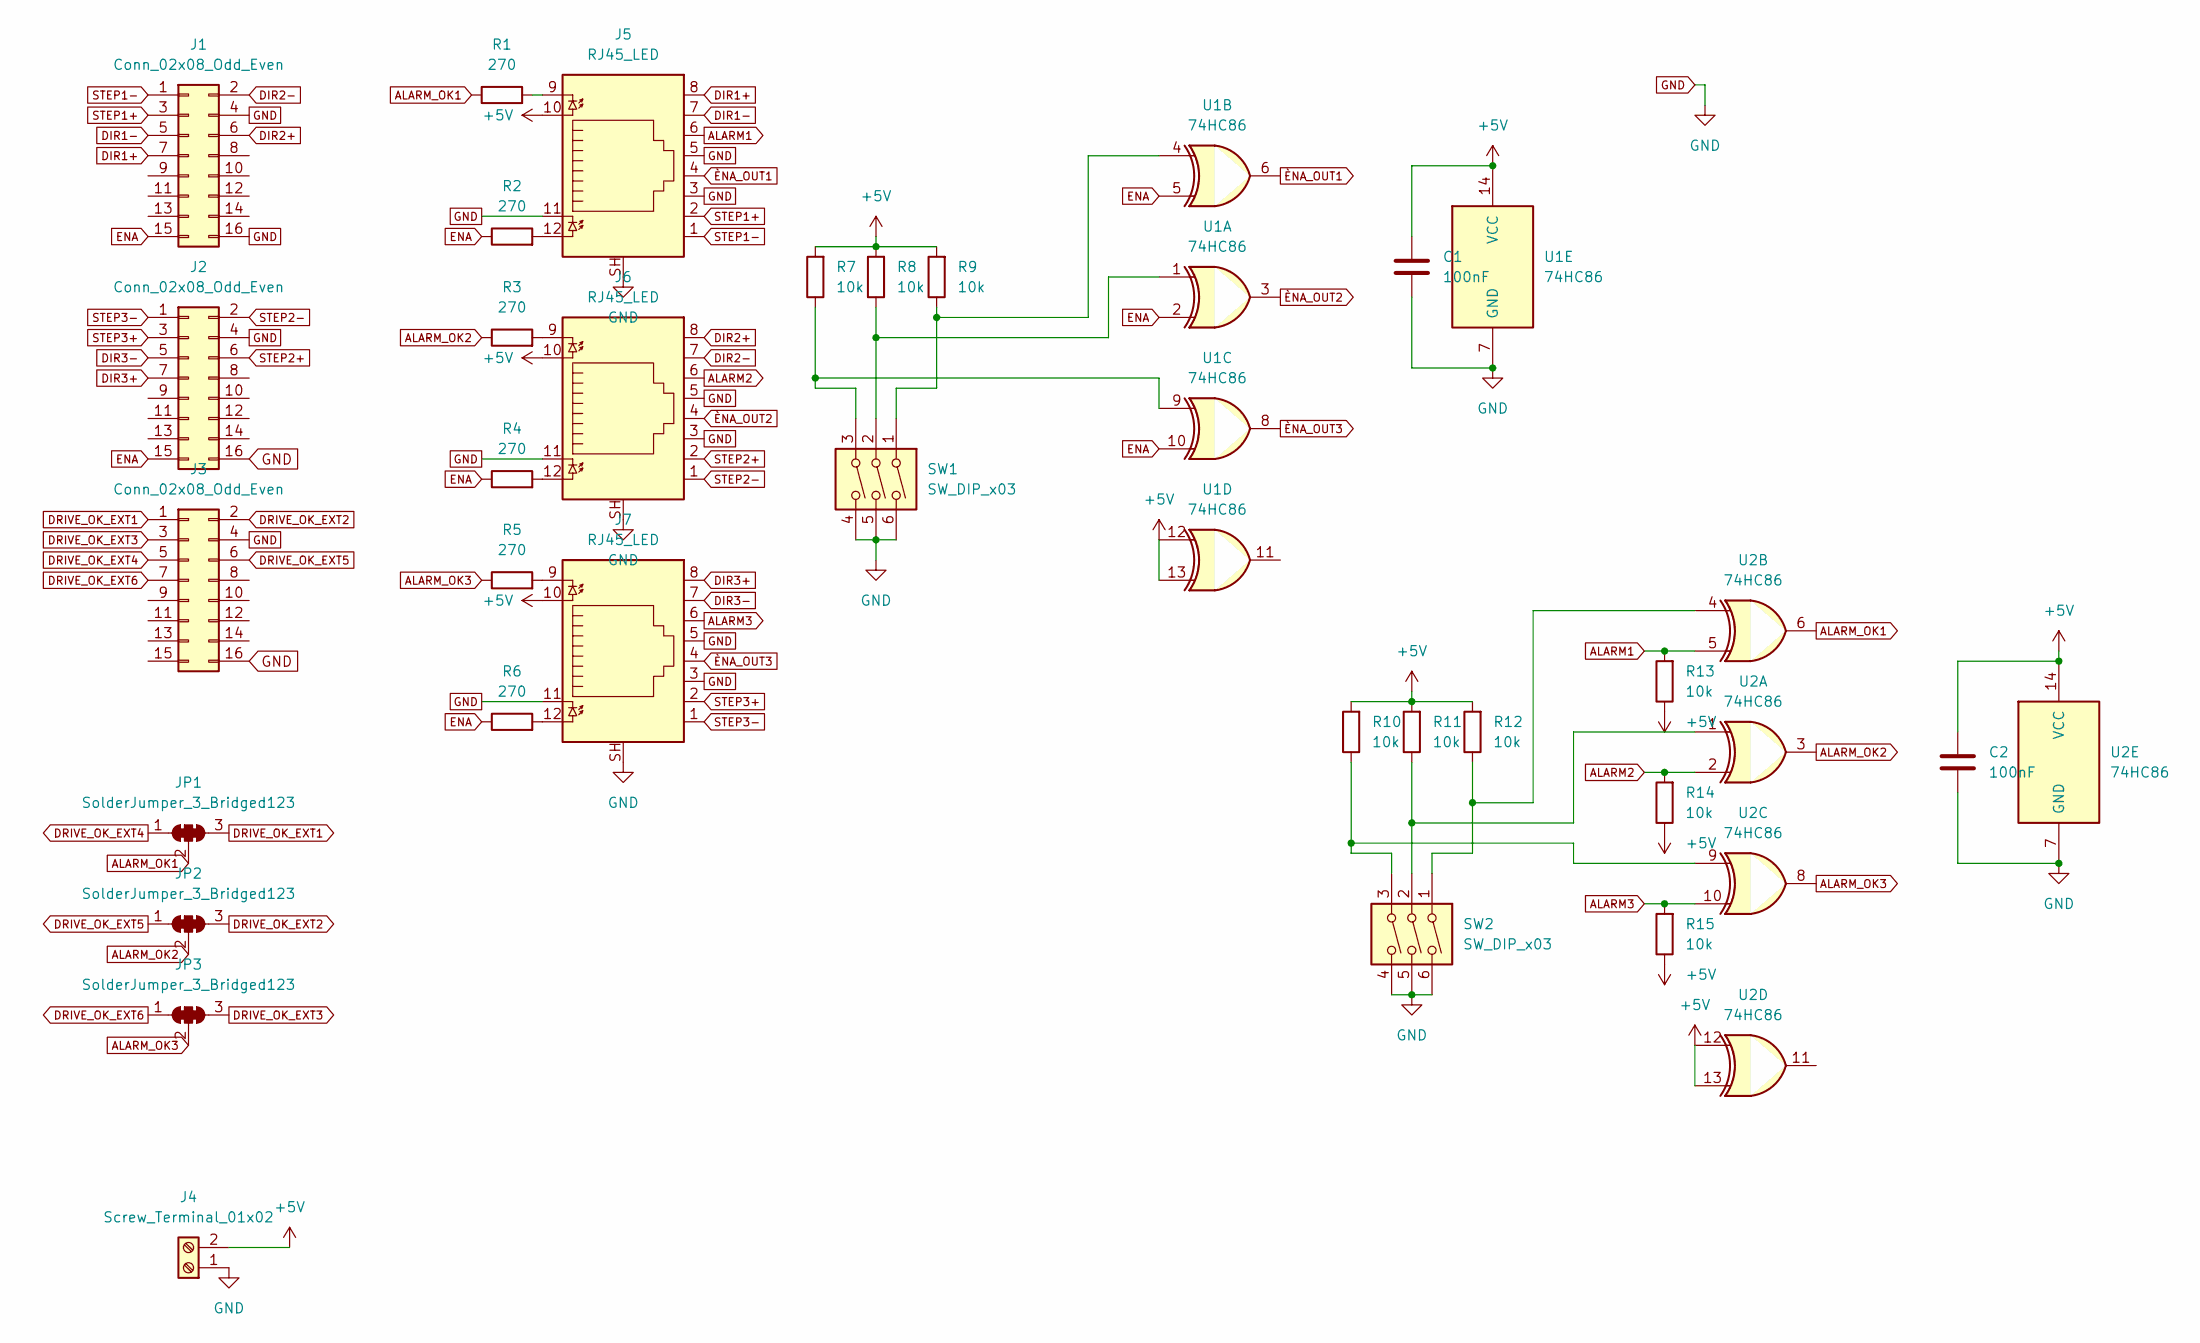
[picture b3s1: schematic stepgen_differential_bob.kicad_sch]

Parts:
C1, C2: 100nF; C_1206_3216Metric_Pad1.33x1.80mm_HandSolder
J1, J2, J3: Conn_02x08_Odd_Even; IDC-Header_2x08_P2.54mm_Vertical
J4: Screw_Terminal_01x02; TerminalBlock_Phoenix_PT-1,5-2-3.5-H_1x02_P3.50mm_Horizontal
J5, J6, J7: RJ45_LED; RJ45_BEL_SS74301-00x_Vertical
JP1, JP2, JP3: SolderJumper_3_Bridged123; SolderJumper-3_P2.0mm_Open_TrianglePad1.0x1.5mm_NumberLabels
R1, R2, R3, R4, R5, R6: 270; R_1206_3216Metric_Pad1.30x1.75mm_HandSolder
R7, R8, R9, R10, R11, R12, R13, R14, R15: 10k; R_1206_3216Metric_Pad1.30x1.75mm_HandSolder
SW1, SW2: SW_DIP_x03; DIP-6_W7.62mm
U1, U2: 74HC86; SO-14_5.3x10.2mm_P1.27mm

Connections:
+5V: C1.1, C2.1, J4.2, J5.10, J6.10, J7.10, R7.2, R8.2, R9.2, R10.2, R11.2, R12.2, R13.1, R14.1, R15.1, U1.12, U1.13, U1.14 (VCC), U2.12, U2.13, U2.14 (VCC)
ALARM1: J5.6, R13.2, U2.5
ALARM2: J6.6, R14.2, U2.2
ALARM3: J7.6, R15.2, U2.10
ALARM_OK1: JP1.2 (C), R1.1, U2.6
ALARM_OK2: JP2.2 (C), R3.1, U2.3
ALARM_OK3: JP3.2 (C), R5.1, U2.8
DIR1+: J1.7, J5.8
DIR1-: J1.5, J5.7
DIR2+: J1.6, J6.8
DIR2-: J1.2, J6.7
DIR3+: J2.7, J7.8
DIR3-: J2.5, J7.7
DRIVE_OK_EXT1: J3.1, JP1.3 (B)
DRIVE_OK_EXT2: J3.2, JP2.3 (B)
DRIVE_OK_EXT3: J3.3, JP3.3 (B)
DRIVE_OK_EXT4: J3.5, JP1.1 (A)
DRIVE_OK_EXT5: J3.6, JP2.1 (A)
DRIVE_OK_EXT6: J3.7, JP3.1 (A)
ENA: J1.15, J2.15, R2.1, R4.1, R6.1, U1.2, U1.5, U1.10
GND: C1.2, C2.2, J1.4, J1.16, J2.4, J2.16, J3.4, J3.16, J4.1, J5.3, J5.5, J5.11, J5.SH, J6.3, J6.5, J6.11, J6.SH, J7.3, J7.5, J7.11, J7.SH, SW1.4, SW1.5, SW1.6, SW2.4, SW2.5, SW2.6, U1.7 (GND), U2.7 (GND)
unnamed: J5.9, R1.2
unnamed: J5.12, R2.2
unnamed: J6.9, R3.2
unnamed: J6.12, R4.2
unnamed: J7.9, R5.2
unnamed: J7.12, R6.2
unnamed: R7.1, SW1.3, U1.9
unnamed: R8.1, SW1.2, U1.1
unnamed: R9.1, SW1.1, U1.4
unnamed: R10.1, SW2.3, U2.9
unnamed: R11.1, SW2.2, U2.1
unnamed: R12.1, SW2.1, U2.4
STEP1+: J1.3, J5.2
STEP1-: J1.1, J5.1
STEP2+: J2.6, J6.2
STEP2-: J2.2, J6.1
STEP3+: J2.3, J7.2
STEP3-: J2.1, J7.1
ÈNA_OUT1: J5.4, U1.6
ÈNA_OUT2: J6.4, U1.3
ÈNA_OUT3: J7.4, U1.8

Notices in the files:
README.md:
CC BY-NC-SA 4.0
